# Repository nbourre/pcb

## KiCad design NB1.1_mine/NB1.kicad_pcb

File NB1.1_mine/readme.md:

# Description
PCB to extend makeblock mbot ultimate and ranger port.
It gives direct access to the following ports:
- I2C
- 5v - batt power
- Signal 1 and 2. Check Auriga pinout for more info.

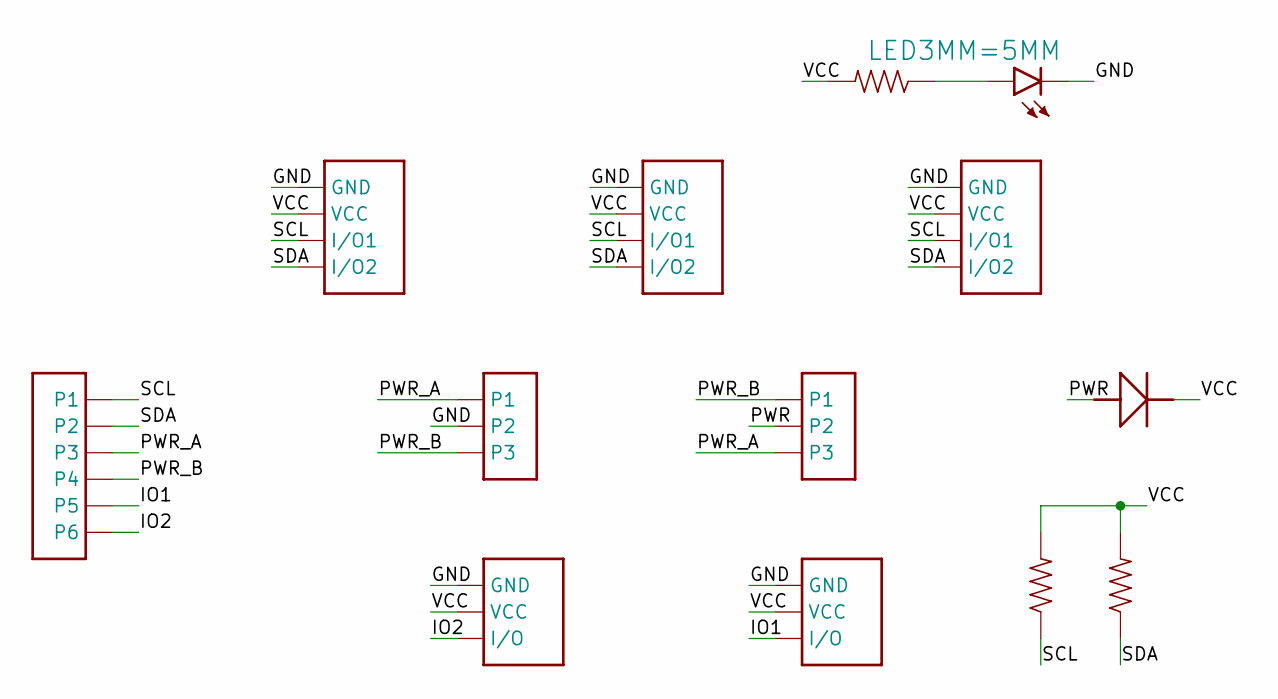
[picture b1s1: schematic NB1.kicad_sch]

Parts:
U$1: DIODE; PIN-8MM
U$2, U$3, U$4: PTH-PLUGIN-4
U$5, U$6: PTH-PLUGIN-3
U$7: PTH-6X1
U$8, U$9: PTH-3X1
U$10, U$11, U$13: RESISTOR; PIN-8MM
U$12: LED3MM=5MM; LED-3MM-5MM

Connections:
GND: U$2.P1 (GND), U$3.P1 (GND), U$4.P1 (GND), U$5.P1 (GND), U$6.P1 (GND), U$9.P2, U$12.K (C)
IO1: U$5.P3 (I/O), U$7.P5
IO2: U$6.P3 (I/O), U$7.P6
unnamed: U$12.A, U$13.P1 (1)
PWR: U$1.P1 (A), U$8.P2
PWR_A: U$7.P3, U$8.P3, U$9.P1
PWR_B: U$7.P4, U$8.P1, U$9.P3
SCL: U$2.P3 (I/O1), U$3.P3 (I/O1), U$4.P3 (I/O1), U$7.P1, U$10.P1 (1)
SDA: U$2.P4 (I/O2), U$3.P4 (I/O2), U$4.P4 (I/O2), U$7.P2, U$11.P1 (1)
VCC: U$1.P2 (K), U$2.P2 (VCC), U$3.P2 (VCC), U$4.P2 (VCC), U$5.P2 (VCC), U$6.P2 (VCC), U$10.P2 (2), U$11.P2 (2), U$13.P2 (2)

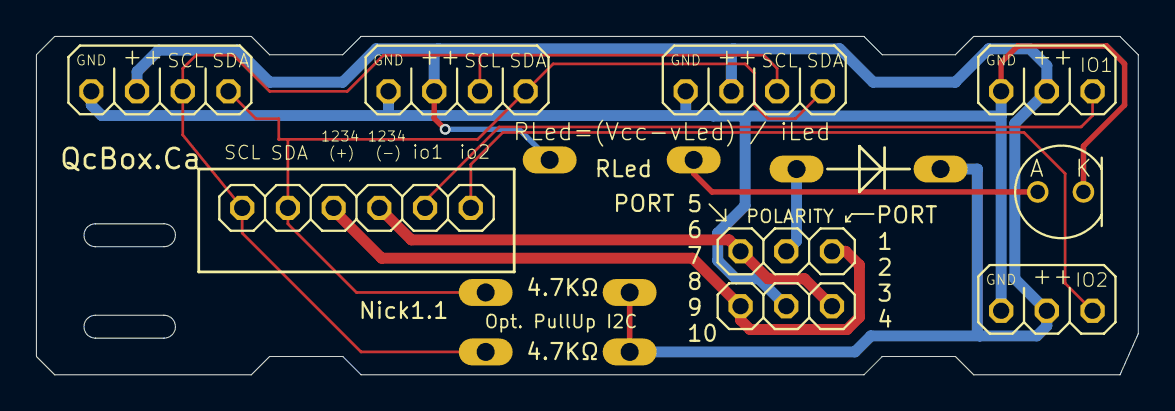
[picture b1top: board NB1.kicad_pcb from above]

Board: 2 copper layers, 61.2 x 18.8 mm, 13 parts (0 on the bottom side), 10 nets.

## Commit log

2023-09-07 Ajout du readme
